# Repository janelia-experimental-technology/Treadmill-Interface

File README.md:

# Treadmill-Interface
Interface to treadmill encoder with USB-serial and analog outputs

Provides an interface to a treadmill that uses an incremental encoder to monitor speed and distance.
The speed and distance are calculated at each increment of the encoder. Time, speed, and distance are sent out a serial-USB port. The minimum time between readinsg can be set, as well as the time to wait to set zero speed.
The absolute value of speed is also sent out to an SMA connector as an analog signal. Direction is sent out another SMA connector as a 3.3V digital signal. 
The design utilizes a Teensy 4.0.
The encoder voltage provided is 5 volts.

PCB design done in Eagle
Firmware design in Arduino with Teensy extensions
Processor - Teensy 4.0

**Opportunity:** Free to make for Non-Profit Research by downloading the design here. See included hardware license.

Commercial licenses are also available, contact innovation@janelia.hhmi.org and reference this DOI.

For inquiries, please contact [innovation@janelia.hhmi.org](mailto:innovation@janelia.hhmi.org) and reference: Janelia 2017-055

To cite the designs, please cite this DOI: [https://doi.org/10.25378/janelia.33179270](https://doi.org/10.25378/janelia.33179270)

**Related to:** https://doi.org/10.25378/janelia.24691311, item 2017-049

**Other:** supersedes Flintbox ID: 2017-055

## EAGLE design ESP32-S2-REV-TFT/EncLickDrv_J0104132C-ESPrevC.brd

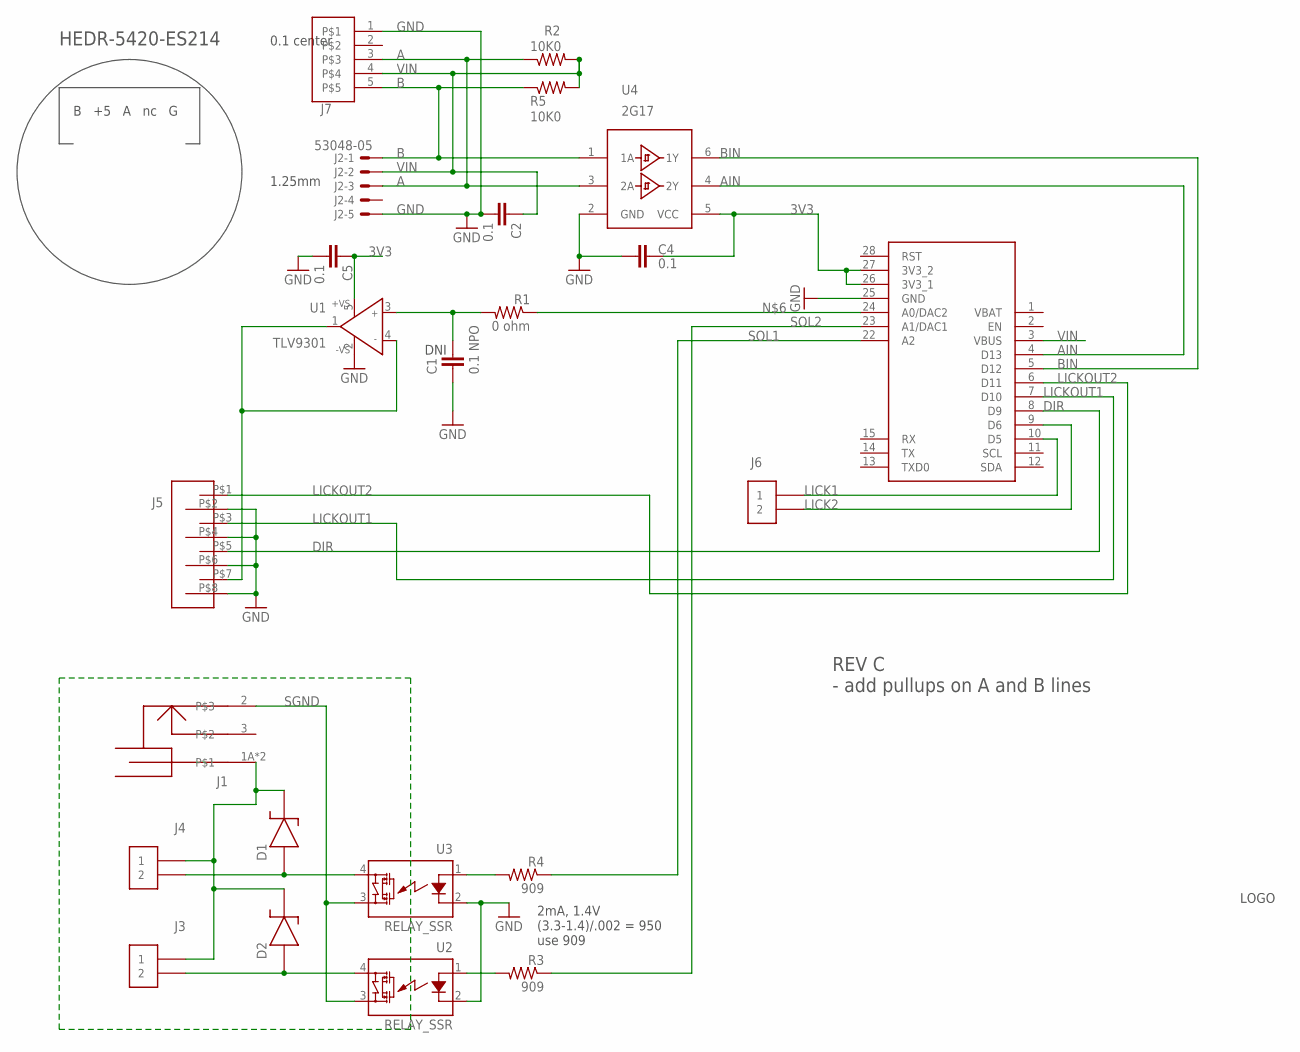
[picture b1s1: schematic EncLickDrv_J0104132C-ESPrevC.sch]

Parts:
C1: 0.1 NPO; 1206S
C2, C4, C5: 0.1; 0603S
D1, D2: DIODE_SCHOTTKYPWRDI-123; PWRDI-123
J1: POWER_JACK_SHUNTPJ-002; PJ-002
J2: 53048-05
J3, J4, J6: CON21881558; 1881558
J5: CON81844743; 1844743
J7: CON5104361-4; 104361-4
M1: ESP32=S2-REV-TFT-NO16-21; ESP32-S2-REV-TFT-NO16-21
R1: 0 ohm; 0805S
R2, R5: 10K0; 0805S
R3, R4: 909; 0805S
U1: TLV9301; SOT23-5
U2, U3: RELAY_SSR; SSR_SOIP
U4: 2G17; SOT23-6
U$1: JFRC-LOGOLOGO_OP; LOGO_BMP_OP

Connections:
3V3: C4.1, C5.1, M1.26 (3V3_1), M1.27 (3V3_2), U1.5 (+VS), U4.5 (VCC)
A: J2.3, J7.3, R2.1, U4.3 (2A)
AIN: M1.4 (D13), U4.4 (2Y)
B: J2.1, J7.5, R5.1, U4.1 (1A)
BIN: M1.5 (D12), U4.6 (1Y)
DIR: J5.P$5 (5), M1.8 (D9)
GND: C1.2, C2.2, C4.2, C5.2, J2.5, J5.P$2 (2), J5.P$4 (4), J5.P$6 (6), J5.P$8 (8), J7.1, M1.25 (GND), U1.2 (-VS), U2.2 (K), U3.2 (K), U4.2 (GND)
LICK1: J6.1, M1.10 (D5)
LICK2: J6.2, M1.9 (D6)
LICKOUT1: J5.P$3 (3), M1.7 (D10)
LICKOUT2: J5.P$1 (1), M1.6 (D11)
unnamed: D1.A, J4.2, U3.4 (DS1)
unnamed: D2.A, J3.2, U2.4 (DS1)
unnamed: D1.K, D2.K, J1.1A, J1.1B, J3.1, J4.1
unnamed: M1.24 (A0/DAC2), R1.1
unnamed: R4.2, U3.1 (A)
unnamed: R3.2, U2.1 (A)
unnamed: J5.P$7 (7), U1.1 (OUT), U1.4 (IN-)
unnamed: C1.1, R1.2, U1.3 (IN+)
SGND: J1.2, U2.3 (DS2), U3.3 (DS2)
SOL1: M1.22 (A2), R4.1
SOL2: M1.23 (A1/DAC1), R3.1
VIN: C2.1, J2.2, J7.4, M1.3 (VBUS), R2.2, R5.2

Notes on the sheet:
B +5 A nc G
HEDR-5420-ES214
1.25mm
2mA, 1.4V (3.3-1.4)/.002 = 950 use 909
DNI
0.1 center
REV C - add pullups on A and B lines

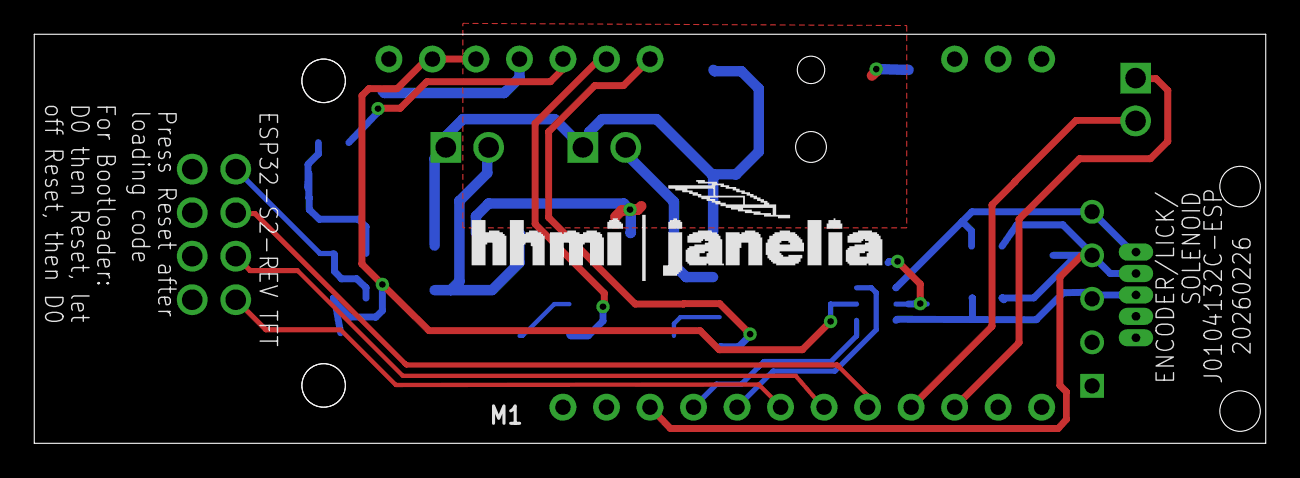
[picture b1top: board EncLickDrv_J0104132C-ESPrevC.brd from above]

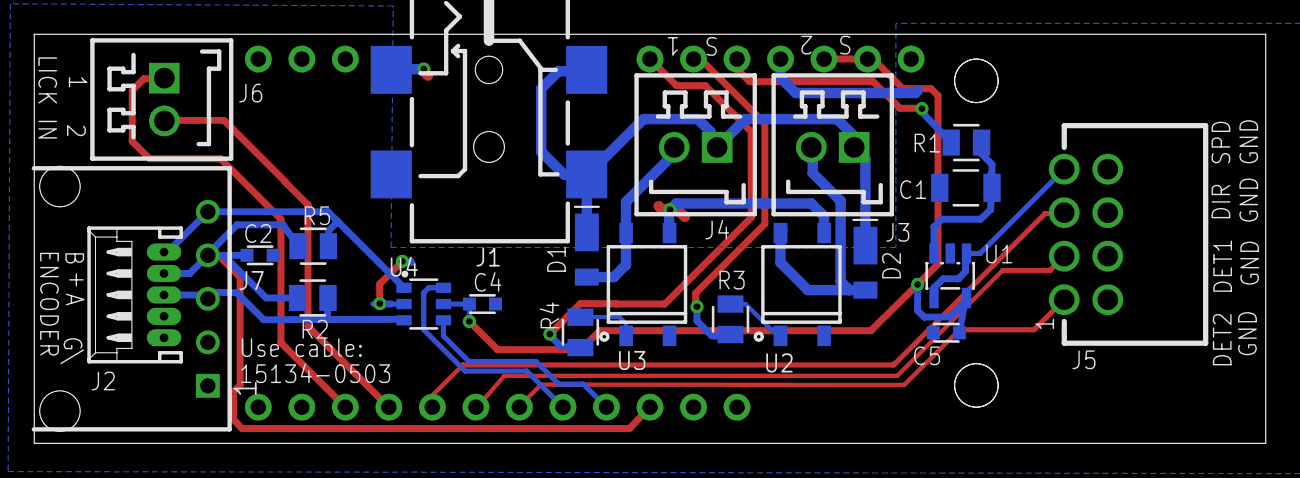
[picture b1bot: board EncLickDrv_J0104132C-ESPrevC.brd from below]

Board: 2 copper layers, 71.9 x 23.9 mm, 24 parts (23 on the bottom side), 23 nets.

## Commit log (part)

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2026-01-07 ESO board and housing
2026-02-24 ADD FW
2026-02-25 add ID command
2026-03-01 add pullups
2026-03-02 Added software files for data acquisition from multiple treadmills at the same time Updated the encoder board firmware to operate at 10Hz instead of 50Hz
2026-03-31 make zero offset functional in EncoderInterfaceT4

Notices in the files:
parts and their libraries:
SparkFun: Licensing: CC v3.0 Share-Alike You are welcome to use this library for commercial purposes.
